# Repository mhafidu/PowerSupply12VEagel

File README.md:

Komponen
1.Casitor Polarisasi 1000uF dan 1uF
2.7812
4.N14004

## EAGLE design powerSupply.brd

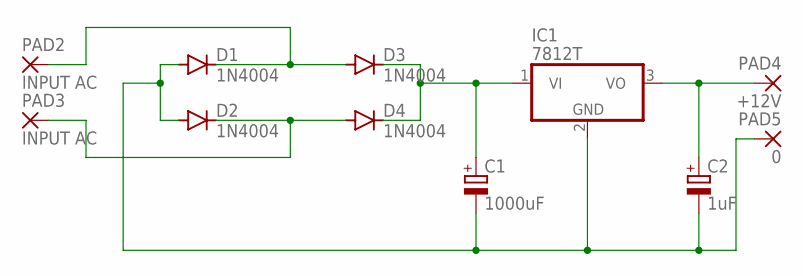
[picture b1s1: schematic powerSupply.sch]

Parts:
C1: 1000uF; E3,5-10
C2: 1uF; E2,5-5
D1, D2, D3, D4: 1N4004; DO41-10
IC1: 7812T; TO220H
PAD2, PAD3: INPUT AC; 2,54/1,0
PAD4: +12V; 2,54/1,0
PAD5: 0; 2,54/1,0

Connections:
unnamed: D1.C, D3.A, PAD2.1
unnamed: D2.C, D4.A, PAD3.1
unnamed: C1.+, D3.C, D4.C, IC1.1 (VI)
unnamed: C2.+, IC1.3 (VO), PAD4.1
unnamed: C1.-, C2.-, D1.A, D2.A, IC1.2 (GND), PAD5.1

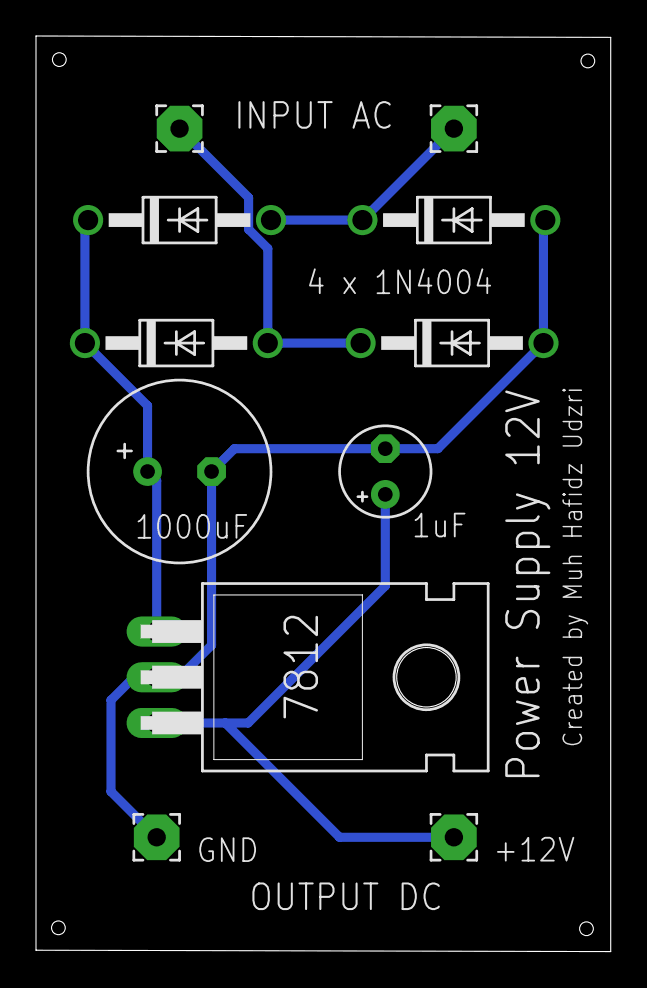
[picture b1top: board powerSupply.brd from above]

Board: 2 copper layers, 31.9 x 50.9 mm, 11 parts (0 on the bottom side), 5 nets.
